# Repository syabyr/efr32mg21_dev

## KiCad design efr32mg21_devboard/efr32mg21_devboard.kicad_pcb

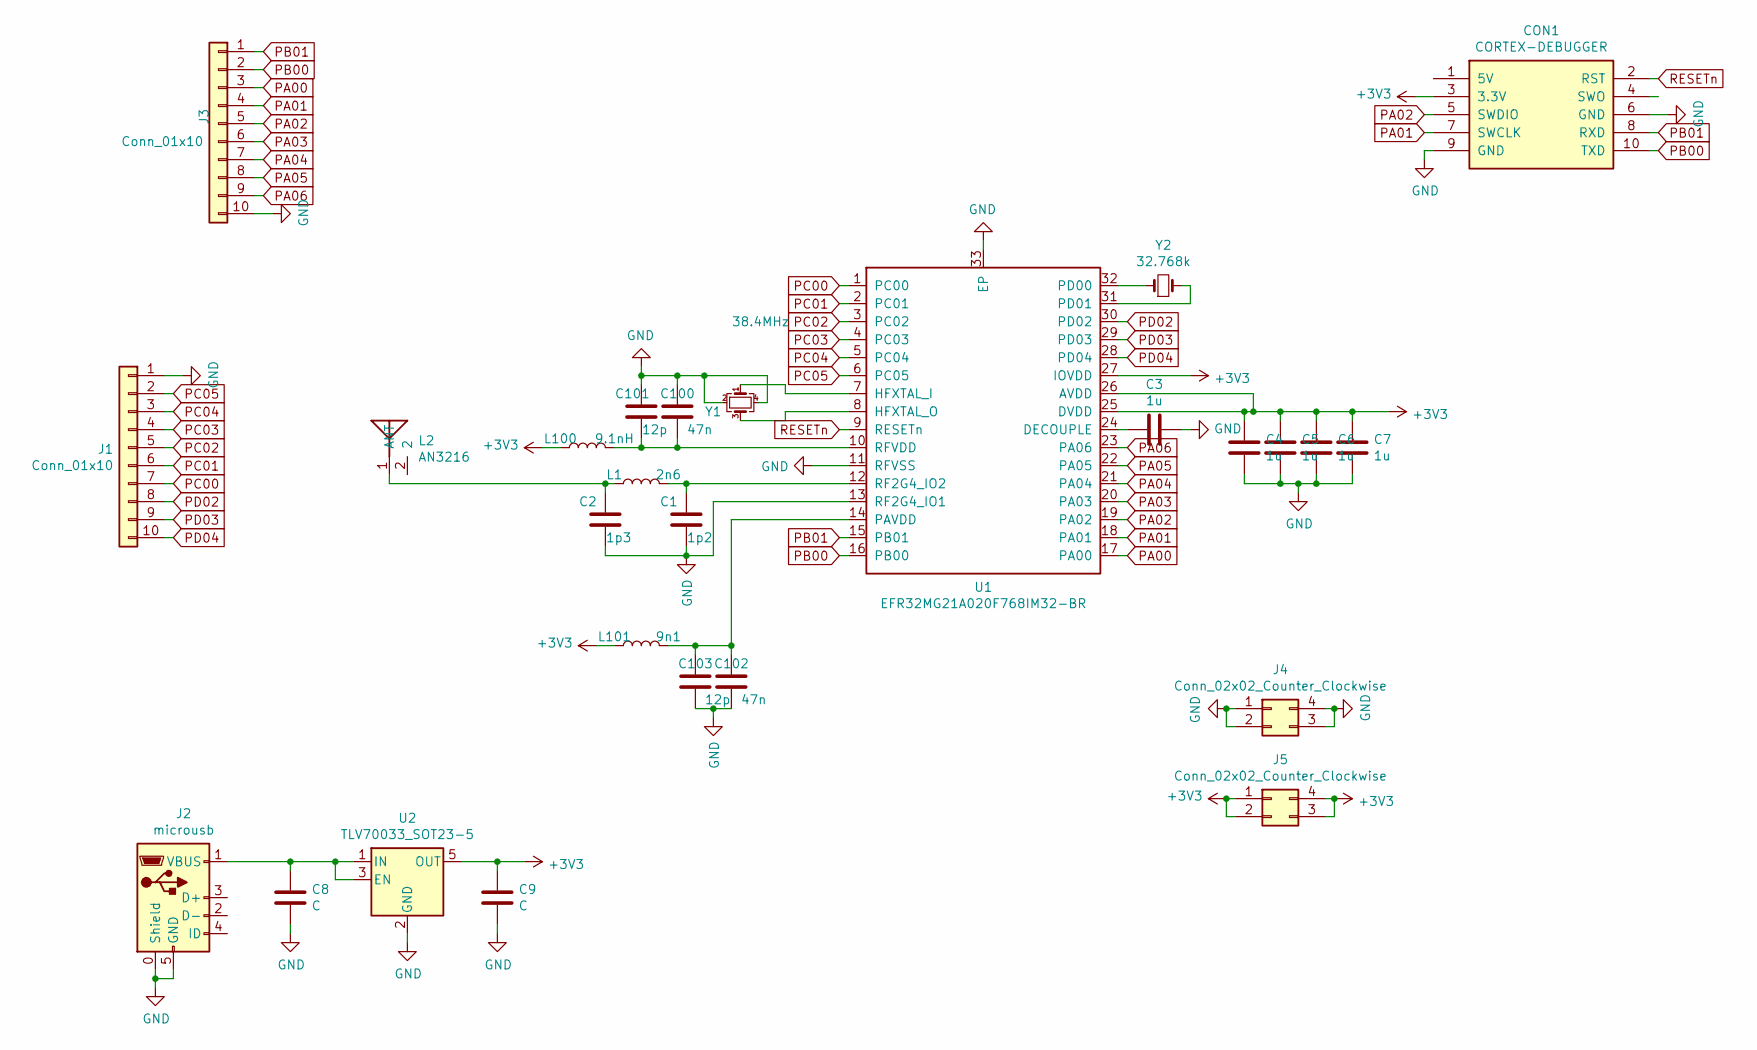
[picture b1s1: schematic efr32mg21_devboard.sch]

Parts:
C1: 1p2; C_0402_1005Metric
C2: 1p3; C_0402_1005Metric
C3, C4, C5, C6, C7: 1u; C_0402_1005Metric
C8, C9: C; C_1206_3216Metric
C100, C102: 47n; C_0402_1005Metric
C101, C103: 12p; C_0402_1005Metric
CON1: CORTEX-DEBUGGER; debugger_2x05_P1.27mm_Vertical
J1, J3: Conn_01x10; PinHeader_1x10_P2.54mm_Vertical
J2: microusb; MICRO-USB_MICRO-USB-17
J4, J5: Conn_02x02_Counter_Clockwise; PinHeader_2x02_P2.54mm_Vertical
L1: 2n6; L_0402_1005Metric
L2: AN3216; ANT3216-2.4G
L100: 9.1nH; L_0603_1608Metric
L101: 9n1; L_0603_1608Metric
U1: EFR32MG21A020F768IM32-BR; QFN-32-1EP_4x4mm_P0.4mm_EP2.9x2.9mm
U2: TLV70033_SOT23-5; SOT-23-5
Y1: 38.4MHz; Crystal_SMD_3225-4Pin_3.2x2.5mm
Y2: 32.768k; Crystal_SMD_3215-2Pin_3.2x1.5mm

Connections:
+3V3: C4.2, C5.2, C6.2, C7.2, C9.1, CON1.3 (3.3V), J5.1, J5.2, J5.3, J5.4, L100.1, L101.1, U1.25 (DVDD), U1.26 (AVDD), U1.27 (IOVDD), U2.5 (OUT)
GND: C1.1, C2.1, C3.1, C4.1, C5.1, C6.1, C7.1, C8.2, C9.2, C100.2, C101.2, C102.1, C103.1, CON1.6 (GND), CON1.9 (GND), J1.1, J2.0 (Shield), J2.5 (GND), J3.10, J4.1, J4.2, J4.3, J4.4, U1.11 (RFVSS), U1.13 (RF2G4_IO1), U1.33 (EP), U2.2 (GND), Y1.2, Y1.4
unnamed: C1.2, L1.2, U1.12 (RF2G4_IO2)
unnamed: C2.2, L1.1, L2.1 (ANT)
unnamed: C3.2, U1.24 (DECOUPLE)
unnamed: C8.1, J2.1 (VBUS), U2.1 (IN), U2.3 (EN)
unnamed: C100.1, C101.1, L100.2, U1.10 (RFVDD)
unnamed: C102.2, C103.2, L101.2, U1.14 (PAVDD)
unnamed: U1.7 (HFXTAL_I), Y1.1
unnamed: U1.8 (HFXTAL_O), Y1.3
unnamed: U1.31 (PD01), Y2.2
unnamed: U1.32 (PD00), Y2.1
PA00: J3.3, U1.17 (PA00)
PA01: CON1.7 (SWCLK), J3.4, U1.18 (PA01)
PA02: CON1.5 (SWDIO), J3.5, U1.19 (PA02)
PA03: J3.6, U1.20 (PA03)
PA04: J3.7, U1.21 (PA04)
PA05: J3.8, U1.22 (PA05)
PA06: J3.9, U1.23 (PA06)
PB00: CON1.10 (TXD), J3.2, U1.16 (PB00)
PB01: CON1.8 (RXD), J3.1, U1.15 (PB01)
PC00: J1.7, U1.1 (PC00)
PC01: J1.6, U1.2 (PC01)
PC02: J1.5, U1.3 (PC02)
PC03: J1.4, U1.4 (PC03)
PC04: J1.3, U1.5 (PC04)
PC05: J1.2, U1.6 (PC05)
PD02: J1.8, U1.30 (PD02)
PD03: J1.9, U1.29 (PD03)
PD04: J1.10, U1.28 (PD04)
RESETn: CON1.2 (RST), U1.9 (RESETn)

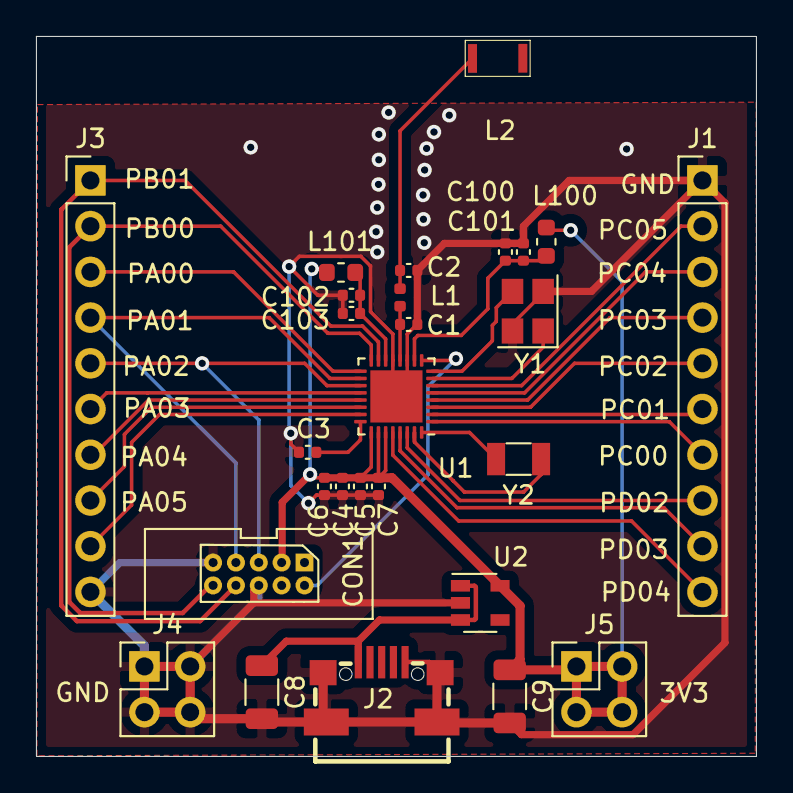
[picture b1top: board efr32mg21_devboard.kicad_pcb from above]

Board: 2 copper layers, 40.0 x 40.0 mm, 27 parts (0 on the bottom side), 31 nets.

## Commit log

2021-05-17 init
2021-05-20 v1.0
